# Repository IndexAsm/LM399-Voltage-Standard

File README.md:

# LM399 10V Voltage Standard

10V Voltage Standard used to calibrate equipment.

## Functions
  - Uptime tracking
  - Temperature tracking
  - Stores calibration data
  - USB connection
  - Status LED
  - Voltage & Current monitoring

## Specifications
  - Calibrated 10 V reference output with ppm-level stability target
  - Low tempco (I am aiming for < 5ppm but that requires testing)
  - Low long term drift ( Also requires testing, in order to determine the value)

## Calibration
  - Short pins on CAL_EN header.
  - Measure the output and adjust the binary trim network accordingly.
  - Connect it to a computer and write changes to eeprom (a special program will be created after constructing the first prototype).
  - Open CAL_EN header.
  - Done!

## Reference
LM399 is chosen as the main reference, which is later amplified to precise 10V with LT1001. It uses precise Z Foil resistors for gain.
It has an internal heater to keep it at stable temperature, in order to prevent output drift.

## PCB
I decided to go with a 4 layer board. This way I can make L2 a solid ground and L3 power. It not only simplifies routing but also improves performance
There is a little space left empty which also has a purpose. This way I can keep digital and power electronics away from sensitive reference part. Voltage regulator can heat up. If they were close to precision section, the trim network would heat up, which would result in output drift.

The reference section has an exposed copper area on the first layer to attach aluminum shielding.

Also there are a few text fields to input measurements, when the device is first calibrated.

## Gallery

## Software
I used Kicad to design this board.

## [BOM](LM399VoltageStandard.csv)
Total cost: 473,59zł + shipping
That is $127.10 USD
Some parts are left with no price or link. That means I already have them so I did not include them in price calculation.

## Credits
I relied on MarcoReps's videos to learn everything in order to make this project.

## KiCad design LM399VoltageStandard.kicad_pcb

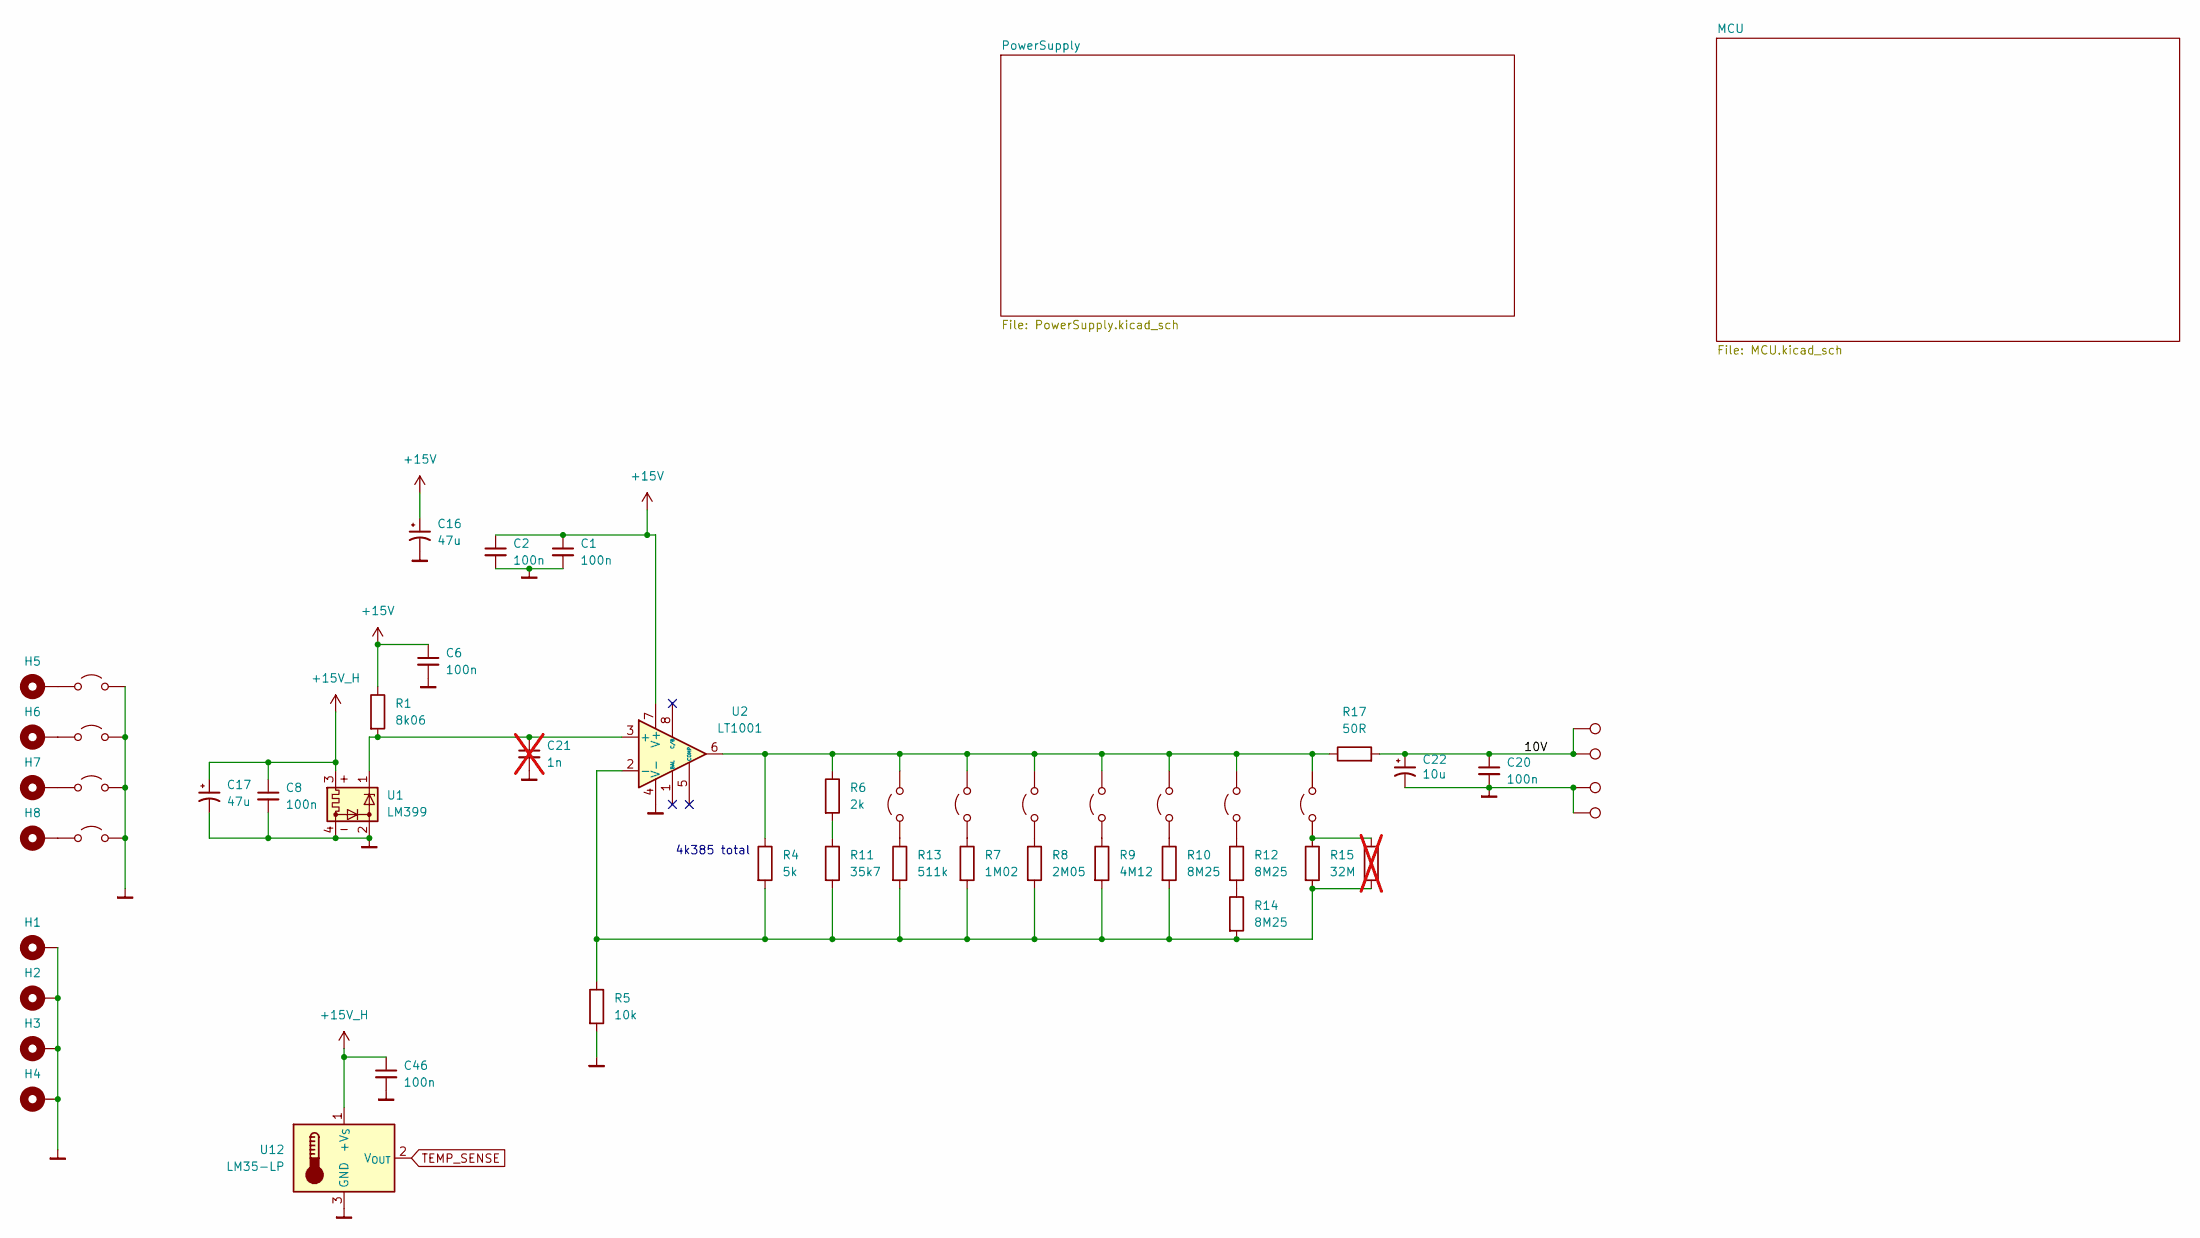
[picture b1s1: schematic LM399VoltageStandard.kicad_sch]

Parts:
C1, C2, C6, C8, C20, C46: 100n; C_0603_1608Metric
C16, C17: 47u; CP_Radial_D5.0mm_P2.00mm
C21: 1n; C_0603_1608Metric; not fitted
C22: 10u; CP_EIA-7132-20_AVX-U
H1, H2, H3, H4, H5, H6, H7, H8: MountingHole_Pad; MountingHole_3.2mm_M3_Pad_TopBottom
JP8, JP9, JP10, JP11, JP12, JP13, JP14, JP15, JP16, JP17, JP18: Jumper_2_Open; SolderJumper-2_P1.3mm_Open_RoundedPad1.0x1.5mm
R1: 8k06; R_0603_1608Metric
R4: 5k; ZFoilResistor
R5: 10k; R_Axial_DIN0207_L6.3mm_D2.5mm_P10.16mm_Horizontal
R6: 2k; R_1206_3216Metric
R7: 1M02; R_0805_2012Metric
R8: 2M05; R_0805_2012Metric
R9: 4M12; R_Axial_DIN0207_L6.3mm_D2.5mm_P10.16mm_Horizontal
R10, R12, R14: 8M25; R_Axial_DIN0204_L3.6mm_D1.6mm_P7.62mm_Horizontal
R11: 35k7; R_0603_1608Metric
R13: 511k; R_0603_1608Metric
R15: 32M; R_Axial_DIN0207_L6.3mm_D2.5mm_P10.16mm_Horizontal
R16: 32M; R_0805_2012Metric; not fitted
R17: 50R; R_0805_2012Metric
TP3, TP6, TP7, TP8: TestPoint; TestPoint_Pad_4.0x4.0mm
U1: LM399; Analog_TO-46-4_ThermalShield
U2: LT1001; SOIC-8_3.9x4.9mm_P1.27mm
U12: LM35-LP; TO-92_Inline

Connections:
+15V: C1.1, C2.1, C6.1, C16.1, R1.1, U2.7 (V+); also elsewhere on the board
+15V_H: C8.1, C17.1, C46.1, U1.3, U12.1 (+V_{S}); also elsewhere on the board
/10V: C20.1, C22.1, R17.2, TP3.1 (1_1), TP7.1 (1_1)
Masa: C1.2, C2.2, C6.2, C8.2, C16.2, C17.2, C20.2, C21.2, C22.2, C46.2, H1.1 (1_1), H2.1 (1_1), H3.1 (1_1), H4.1 (1_1), JP15.2 (B), JP16.2 (B), JP17.2 (B), JP18.2 (B), R5.2, TP6.1 (1_1), TP8.1 (1_1), U1.2, U1.4, U2.4 (V-), U12.3 (GND); also elsewhere on the board
unnamed: JP8.1 (A), R13.1
unnamed: JP9.1 (A), R7.1
unnamed: JP10.1 (A), R8.1
unnamed: JP8.2 (B), JP9.2 (B), JP10.2 (B), JP11.2 (B), JP12.2 (B), JP13.2 (B), JP14.2 (B), R4.1, R6.1, R17.1, U2.6
unnamed: JP11.1 (A), R9.1
unnamed: JP12.1 (A), R10.1
unnamed: JP13.1 (A), R12.1
unnamed: JP14.1 (A), R15.1, R16.1
unnamed: H5.1 (1_1), JP15.1 (A)
unnamed: H6.1 (1_1), JP16.1 (A)
unnamed: H7.1 (1_1), JP17.1 (A)
unnamed: H8.1 (1_1), JP18.1 (A)
unnamed: R6.2, R11.1
unnamed: R12.2, R14.1
unnamed: C21.1, R1.2, U1.1, U2.3 (+)
unnamed: R4.2, R5.1, R7.2, R8.2, R9.2, R10.2, R11.2, R13.2, R14.2, R15.2, R16.2, U2.2 (-)
TEMP_SENSE: U12.2 (V_{OUT}); also elsewhere on the board

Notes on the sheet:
4k385 total

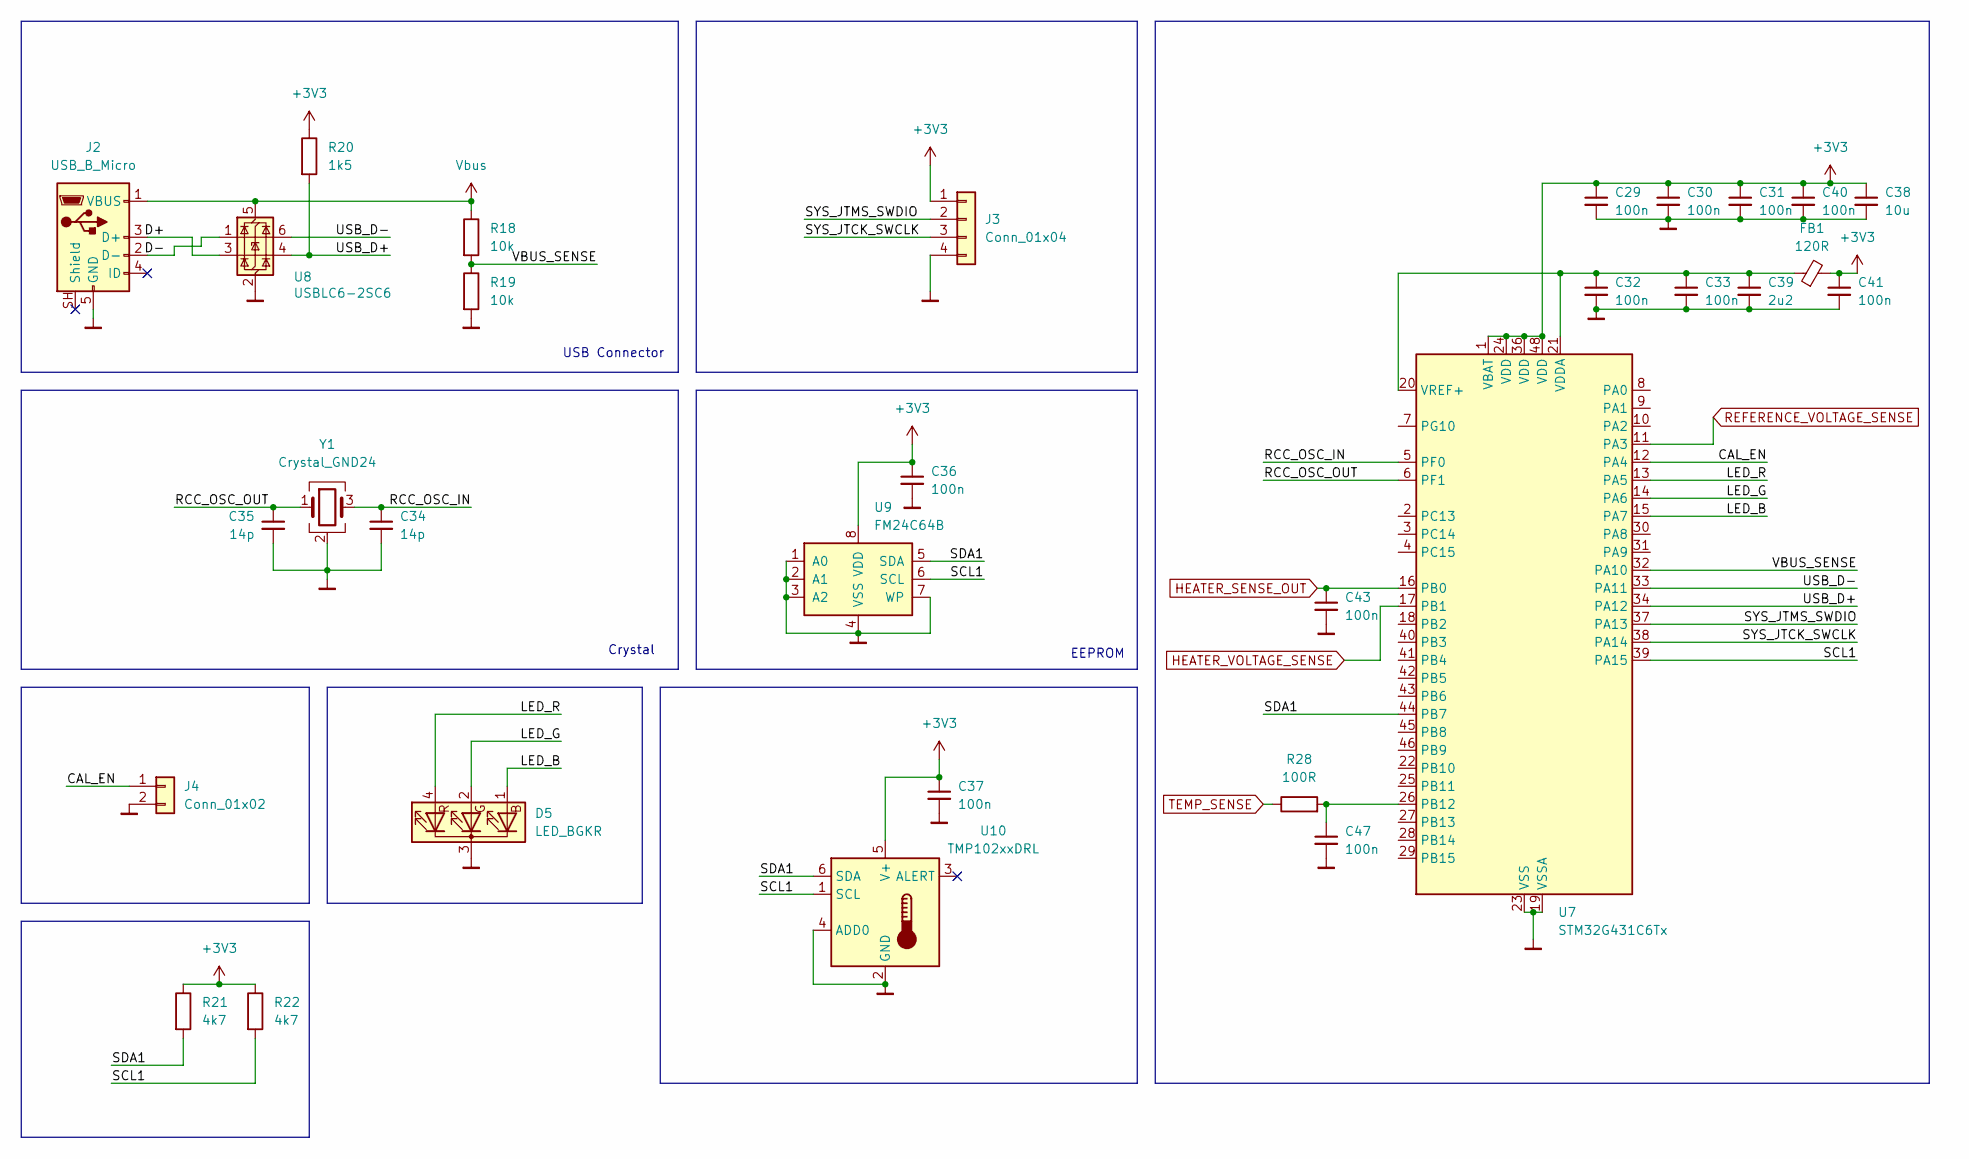
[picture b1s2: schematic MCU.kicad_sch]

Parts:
C29, C30, C31, C32, C33, C36, C37, C40, C41, C43, C47: 100n; C_0603_1608Metric
C34, C35: 14p; C_0603_1608Metric
C38: 10u; C_0805_2012Metric
C39: 2u2; C_0603_1608Metric
D5: LED_BGKR; LED_D5.0mm-4_RGB_Wide_Pins
FB1: 120R; L_0603_1608Metric
J2: USB_B_Micro; USB_Micro-B_Technik_TWP-4002D-H3
J3: Conn_01x04; PinHeader_1x04_P2.54mm_Vertical
J4: Conn_01x02; PinHeader_1x02_P2.54mm_Vertical
R18, R19: 10k; R_0603_1608Metric
R20: 1k5; R_0603_1608Metric
R21, R22: 4k7; R_0603_1608Metric
R28: 100R; R_0603_1608Metric
U7: STM32G431C6Tx; LQFP-48_7x7mm_P0.5mm
U8: USBLC6-2SC6; SOT-23-6
U9: FM24C64B; SOIC-8_3.9x4.9mm_P1.27mm
U10: TMP102xxDRL; SOT-563
Y1: Crystal_GND24; Crystal_SMD_EuroQuartz_X22-4Pin_2.5x2.0mm_HandSoldering

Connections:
+3V3: C29.1, C30.1, C31.1, C36.1, C37.1, C38.1, C40.1, C41.1, FB1.2, J3.1, R20.1, R21.1, R22.1, U7.1 (VBAT), U7.24 (VDD), U7.36 (VDD), U7.48 (VDD), U9.8 (VDD), U10.5 (V+); also elsewhere on the board
/MCU/CAL_EN: J4.1, U7.12 (PA4)
/MCU/D+: J2.3 (D+), U8.3 (I/O2)
/MCU/D-: J2.2 (D-), U8.1 (I/O1)
/MCU/LED_B: D5.1 (BA), U7.15 (PA7)
/MCU/LED_G: D5.2 (GA), U7.14 (PA6)
/MCU/LED_R: D5.4 (RA), U7.13 (PA5)
/MCU/RCC_OSC_IN: C34.1, U7.5 (PF0), Y1.3
/MCU/RCC_OSC_OUT: C35.1, U7.6 (PF1), Y1.1
/MCU/SCL1: R22.2, U7.39 (PA15), U9.6 (SCL), U10.1 (SCL)
/MCU/SDA1: R21.2, U7.44 (PB7), U9.5 (SDA), U10.6 (SDA)
/MCU/SYS_JTCK_SWCLK: J3.3, U7.38 (PA14)
/MCU/SYS_JTMS_SWDIO: J3.2, U7.37 (PA13)
/MCU/USB_D+: R20.2, U7.34 (PA12), U8.4 (I/O2)
/MCU/USB_D-: U7.33 (PA11), U8.6 (I/O1)
/MCU/VBUS_SENSE: R18.2, R19.1, U7.32 (PA10)
HEATER_SENSE_OUT: C43.1, U7.16 (PB0); also elsewhere on the board
HEATER_VOLTAGE_SENSE: U7.17 (PB1); also elsewhere on the board
Masa: C29.2, C30.2, C31.2, C32.2, C33.2, C34.2, C35.2, C36.2, C37.2, C38.2, C39.2, C40.2, C41.2, C43.2, C47.2, D5.3 (K), J2.5 (GND), J3.4, J4.2, R19.2, U7.19 (VSSA), U7.23 (VSS), U7.35 (VSS), U7.47 (VSS), U8.2 (GND), U9.1 (A0), U9.2 (A1), U9.3 (A2), U9.4 (VSS), U9.7 (WP), U10.2 (GND), U10.4 (ADD0), Y1.2 (G), Y1.4 (G); also elsewhere on the board
unnamed: C47.1, R28.2, U7.26 (PB12)
unnamed: C32.1, C33.1, C39.1, FB1.1, U7.20 (VREF+), U7.21 (VDDA)
REFERENCE_VOLTAGE_SENSE: U7.11 (PA3); also elsewhere on the board
TEMP_SENSE: R28.1; also elsewhere on the board
Vbus: J2.1 (VBUS), R18.1, U8.5 (VBUS)

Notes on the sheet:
Crystal
EEPROM
USB Connector

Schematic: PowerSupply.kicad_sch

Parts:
C4, C5, C48: 1000u; CP_Radial_D10.0mm_P3.80mm
C7, C10, C18, C19, C24, C25, C26, C42, C44, C45: 100n; C_0603_1608Metric
C9, C14, C23: 47u; CP_Radial_D5.0mm_P2.00mm
C12, C13: 100n; C_0805_2012Metric
C15: PUUP3JH; CP_Radial_D10.0mm_P3.80mm
C27, C28: 10u; C_0805_2012Metric
D2, D3, D4: PUUP3JH; TO-277A
D6: B40C2300-1500A; Diode_Bridge_19.0x3.5x10.0mm_P5.0mm
J1: Screw_Terminal_01x02; TerminalBlock_MaiXu_MX126-5.0-02P_1x02_P5.00mm
R23: 0R1; R_0805_2012Metric
R24, R27: 4k; R_0603_1608Metric
R25, R26: 20k; R_0603_1608Metric
TP2, TP4, TP5: TestPoint; TestPoint_Pad_D1.5mm
U4: TLV75533PDRV; WSON-6-1EP_2x2mm_P0.65mm_EP1x1.6mm
U5, U13: LM7815; TO-220-3_Vertical
U6: LM7805_TO220; TO-220-3_Vertical
U11: INA180B3; SOT-23-5

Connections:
+3V3: C26.1, C27.1, C42.1, U4.1 (OUT), U11.5 (V+); also elsewhere on the board
+5V: C18.1, C24.1, C28.1, U4.4 (EN), U4.6 (IN), U6.3 (VO)
+15V: C9.1, C10.1, R25.1, TP4.1 (1_1), U13.3 (VO); also elsewhere on the board
+15V_H: C13.1, C14.1, R26.1, TP2.1 (1_1), U5.3 (VO); also elsewhere on the board
/PowerSupply/HEATER_SENSE_L: C12.1, C15.1, R23.2, U5.1 (VI), U11.3 (-)
HEATER_SENSE_OUT: U11.4; also elsewhere on the board
HEATER_VOLTAGE_SENSE: C45.1, R26.2, R27.1; also elsewhere on the board
Masa: C4.2, C5.2, C7.2, C9.2, C10.2, C12.2, C13.2, C14.2, C15.2, C18.2, C19.2, C23.2, C24.2, C25.2, C26.2, C27.2, C28.2, C42.2, C44.2, C45.2, C48.2, D6.1 (-), R24.2, R27.2, TP5.1 (1_1), U4.3 (GND), U4.7 (GND), U5.2 (GND), U6.2 (GND), U11.2 (GND), U13.2 (GND); also elsewhere on the board
unnamed: D6.3, J1.1
unnamed: D6.2, J1.2
REFERENCE_VOLTAGE_SENSE: C44.1, R24.1, R25.2; also elsewhere on the board
VIN: C4.1, C5.1, C7.1, C19.1, C23.1, C25.1, C48.1, D6.4 (+), R23.1, U6.1 (VI), U11.1 (+), U13.1 (VI)

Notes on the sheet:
DP-241-4-16
Voltage Monitoring
Rectifier and filtering
Current Monitoring
Digital supply
Reference 15V
Heater 15V

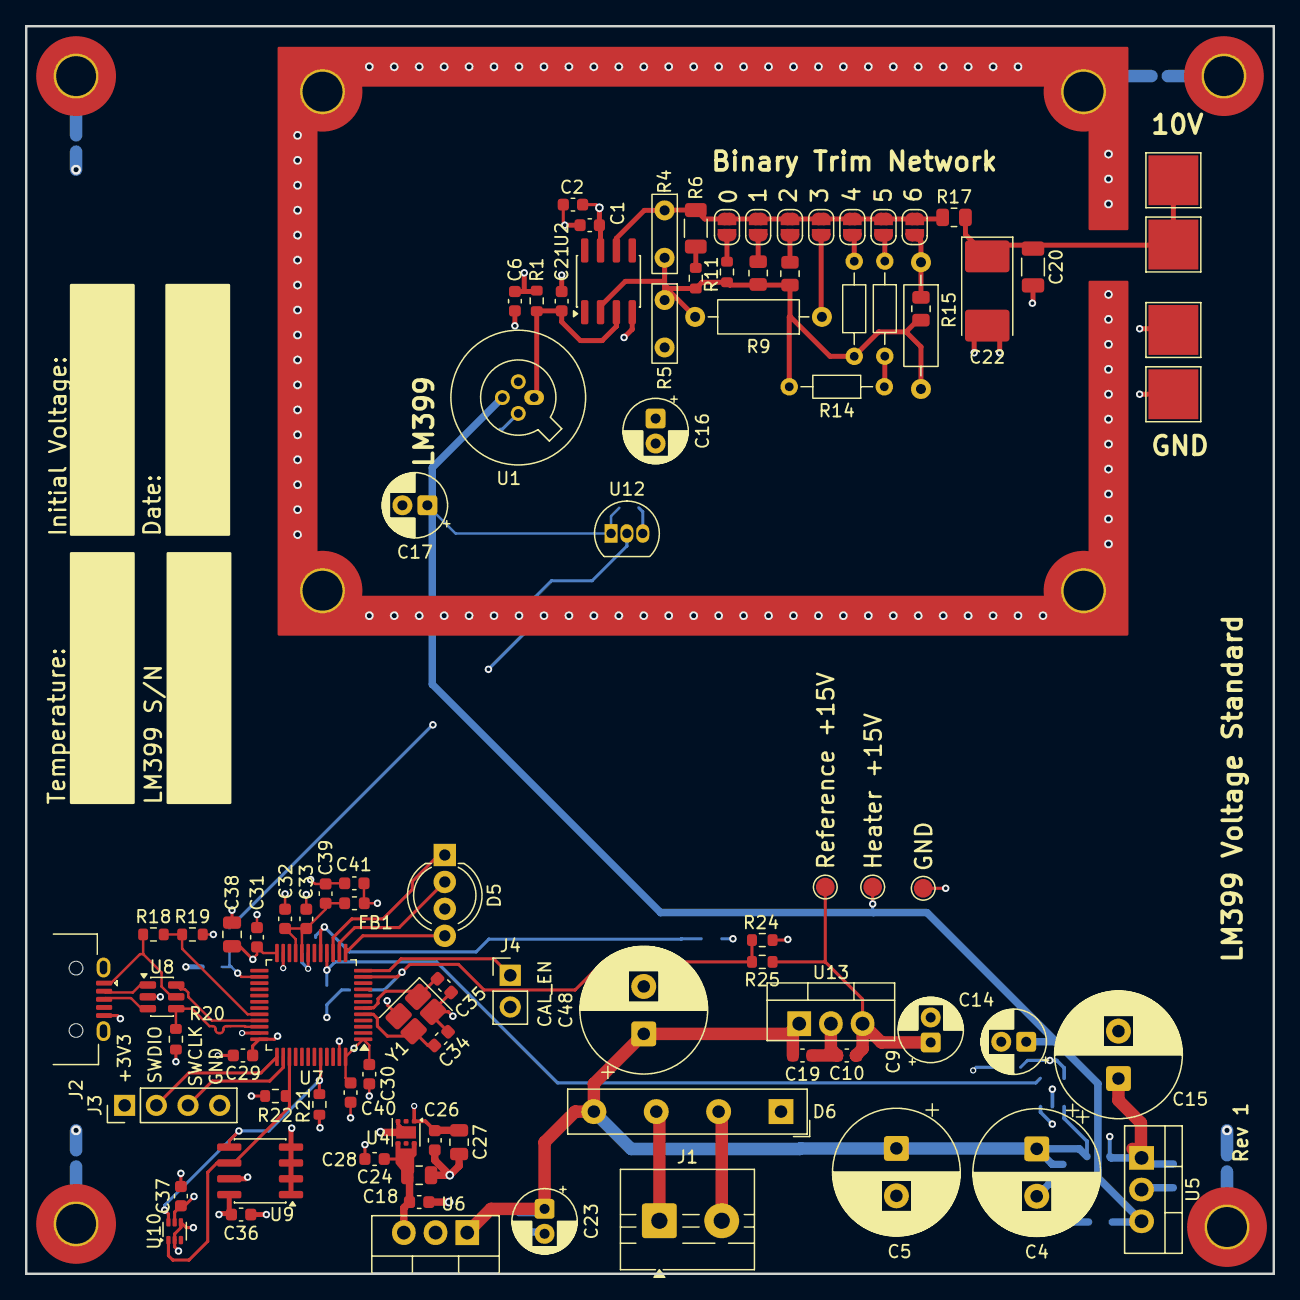
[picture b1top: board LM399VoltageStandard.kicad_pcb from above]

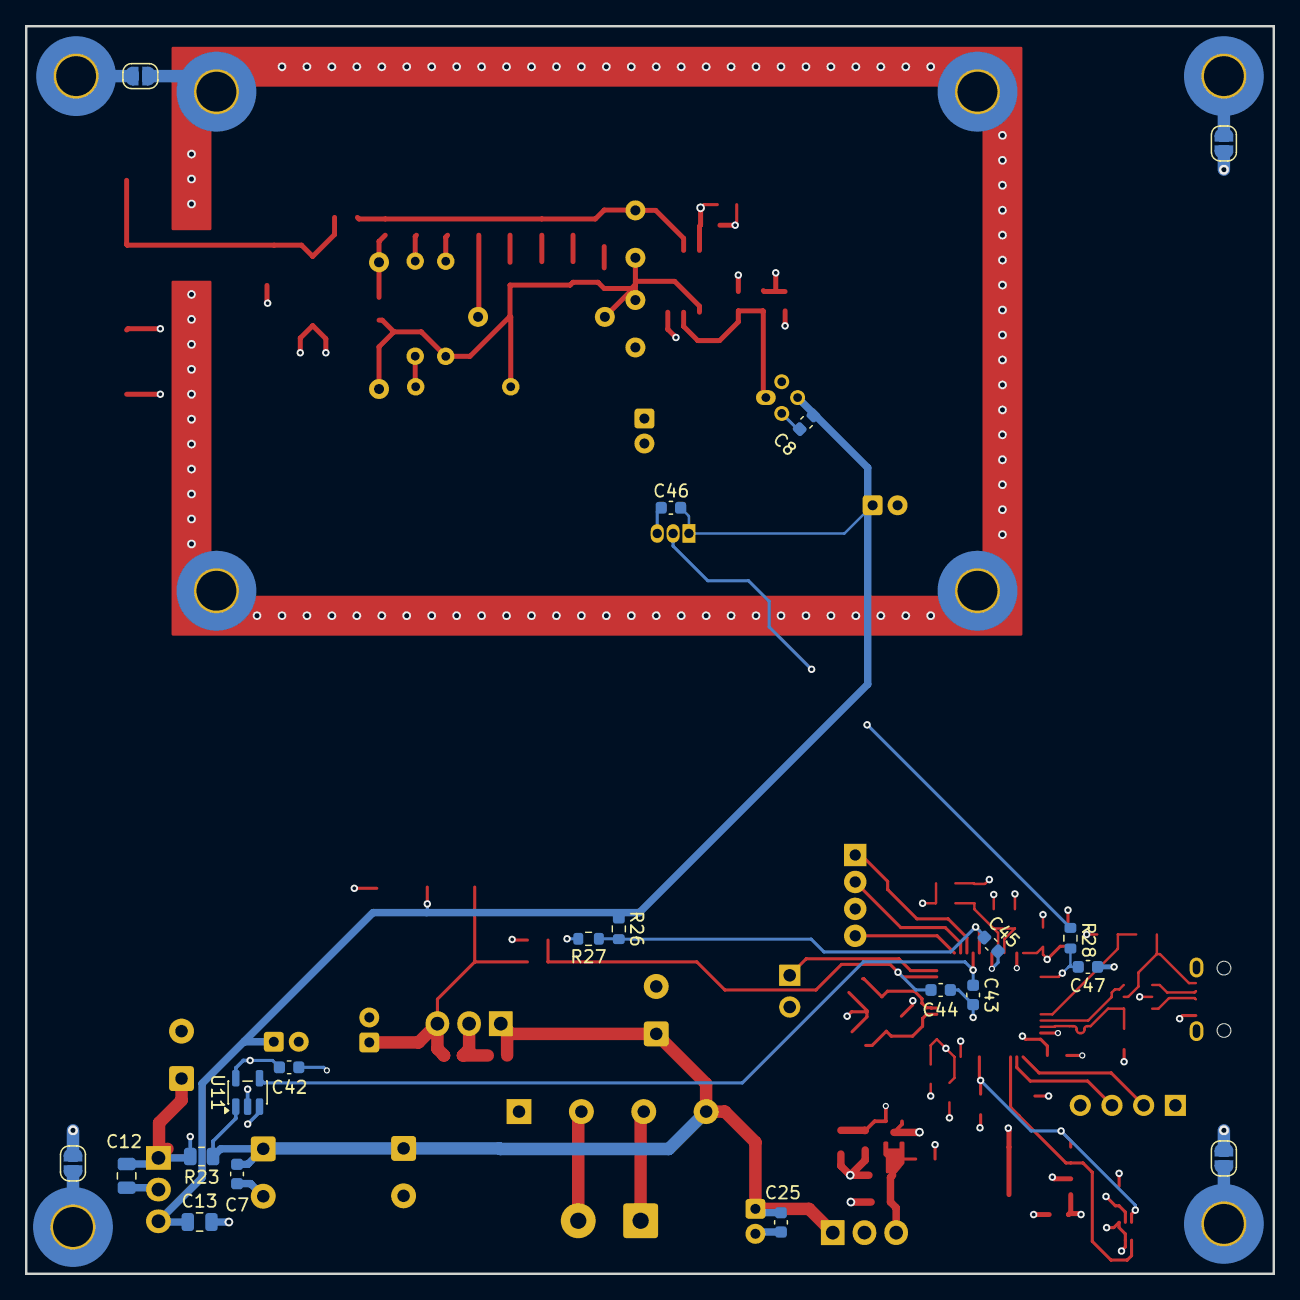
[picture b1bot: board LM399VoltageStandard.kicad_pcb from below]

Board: 4 copper layers, 100.0 x 100.0 mm, 118 parts (20 on the bottom side), 48 nets.

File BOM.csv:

"Reference","Qty","Value","DNP","Price","Link","Footprint"
"C1,C2,C6,C7,C8,C10,C11,C18,C19,C24,C25,C26,C29,C30,C31,C32,C33,C36,C37,C40,C41,C42,C43,C44,C45,C46,C47","27","100n","","","","Capacitor_SMD:C_0603_1608Metric"
"C4,C5,C15","3","1000u","","","","Capacitor_THT:CP_Radial_D10.0mm_P3.80mm"
"C9,C14,C16,C17,C23","5","47u","","","","Capacitor_THT:CP_Radial_D5.0mm_P2.00mm"
"C12,C13","2","100n","","","","Capacitor_SMD:C_0805_2012Metric"
"C20","1","100n","","1,26zł","https://www.mouser.pl/en/ProductDetail/Murata-Electronics/GR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","Capacitor_SMD:C_1206_3216Metric"
"C21","1","1n","DNP","","","Capacitor_SMD:C_0603_1608Metric"
"C22","1","10u","","","https://www.mouser.pl/ProductDetail/KEMET/A700V106M016ATE045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","Capacitor_Tantalum_SMD:CP_EIA-7132-20_AVX-U"
"C27,C28,C38","3","10u","","1,51zł","https://www.mouser.pl/en/ProductDetail/Samsung-Electro-Mecha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","Capacitor_SMD:C_0805_2012Metric"
"C34,C35","2","14p","","","","Capacitor_SMD:C_0603_1608Metric"
"C39","1","2u2","","0,36zł ","https://www.mouser.pl/en/ProductDetail/Samsung-Electro-Mecha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","Capacitor_SMD:C_0603_1608Metric"
"D6","1","KBP206G","","15.32zł","https://www.mouser.pl/en/ProductDetail/Taiwan-Semiconductor/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", ""
"D5","1","LED_BGKR","","0,97zł","https://www.mouser.pl/en/ProductDetail/Soldered/100105?qs=%2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","LED_THT:LED_D5.0mm-4_RGB_Wide_Pins"
"FB1","1","120R","","0,36zł ","https://www.mouser.pl/en/ProductDetail/TDK/MMZ1608S121ATA00?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","Inductor_SMD:L_0603_1608Metric"
"J1","1","Screw_Terminal_01x02","","","","TerminalBlock:TerminalBlock_MaiXu_MX126-5.0-02P_1x02_P5.00mm"
"J2","1","USB_B_Micro","","","","Connector_USB:USB_Micro-B_Technik_TWP-4002D-H3"
"J3","1","Conn_01x04","","","","Connector_PinHeader_2.54mm:PinHeader_1x04_P2.54mm_Vertical"
"J4","1","Conn_01x02","","","","Connector_PinHeader_2.54mm:PinHeader_1x02_P2.54mm_Vertical"
"JP8,JP9,JP10,JP11,JP12,JP13,JP14,JP15,JP16,JP17,JP18","11","Jumper_2_Open","","","","Jumper:SolderJumper-2_P1.3mm_Open_RoundedPad1.0x1.5mm"
"R1","1","8k06","","2,71zł","https://www.mouser.pl/ProductDetail/TE-Connectivity-Holswort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","Resistor_SMD:R_0603_1608Metric"
"R2","1","250","","","","Resistor_SMD:R_0603_1608Metric"
"R3","1","150k","","","","Resistor_SMD:R_0603_1608Metric"
"R4","1","5k","","141,58zł","https://www.mouser.pl/ProductDetail/Vishay-Precision-Group-F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","LM399VoltageStandard:ZFoilResistor"
"R5","1","10k","","104,75zł","https://www.mouser.pl/ProductDetail/Vishay-Precision-Group-F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","Resistor_THT:R_Axial_DIN0207_L6.3mm_D2.5mm_P10.16mm_Horizontal"
"R6","1","2k","","9,41zł","https://www.mouser.pl/ProductDetail/SEI-Stackpole/RNCF1206TK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","Resistor_SMD:R_1206_3216Metric"
"R7","1","1M02","","1,37zł","https://www.mouser.pl/ProductDetail/YAGEO/RT0805BRD071M02L?q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","Resistor_SMD:R_0805_2012Metric"
"R8","1","2M05","","1,37zł","https://www.mouser.pl/ProductDetail/Kamaya/RGC1-10C2054FTP?q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","Resistor_SMD:R_0805_2012Metric"
"R9","1","4M12","","10,67zł","https://www.mouser.pl/ProductDetail/Vishay-Dale/CMF554M1200F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","Resistor_THT:R_Axial_DIN0207_L6.3mm_D2.5mm_P10.16mm_Horizontal"
"R10,R12,R14","3","8M25","","13,70zł","https://www.mouser.pl/ProductDetail/Xicon/270-8.25M-RC?qs=sG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","Resistor_THT:R_Axial_DIN0204_L3.6mm_D1.6mm_P7.62mm_Horizontal"
"R11","1","35k7","","3,72zł","https://www.mouser.pl/ProductDetail/TE-Connectivity-Holswort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","Resistor_SMD:R_0603_1608Metric"
"R13","1","511k","","2,13zł","https://www.mouser.pl/ProductDetail/TE-Connectivity-Holswort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","Resistor_SMD:R_0603_1608Metric"
"R15","1","32M","","10,67zł","https://www.mouser.pl/ProductDetail/Vishay-Dale/CMF554M1200F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","Resistor_THT:R_Axial_DIN0207_L6.3mm_D2.5mm_P10.16mm_Horizontal"
"R16","1","32M","DNP","","https://www.mouser.pl/ProductDetail/Kamaya/RGC1-10C2054FTP?q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","Resistor_SMD:R_0805_2012Metric"
"R17","1","50R","","1,37","https://www.mouser.pl/ProductDetail/YAGEO/RT0805BRD071M02L?q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","Resistor_SMD:R_0805_2012Metric"
"R18,R19","2","10k","","","","Resistor_SMD:R_0603_1608Metric"
"R20","1","1k5","","","","Resistor_SMD:R_0603_1608Metric"
"R21,R22","2","4k7","","","","Resistor_SMD:R_0603_1608Metric"
"R23","1","0R1","","0,76zł","https://www.mouser.pl/en/ProductDetail/Panasonic/ERJ-6DSJR10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","Resistor_SMD:R_0805_2012Metric"
"R24,R27","2","4k","","","","Resistor_SMD:R_0603_1608Metric"
"R25,R26","2","20k","","","","Resistor_SMD:R_0603_1608Metric"
"R28","1","100R","","","","Resistor_SMD:R_0603_1608Metric"
"TP2,TP4,TP5","3","TestPoint","","","","TestPoint:TestPoint_Pad_D1.5mm"
"TP3,TP6,TP7,TP8","4","TestPoint","","","","TestPoint:TestPoint_Pad_4.0x4.0mm"
"U1","1","LM399","","","https://www.mouser.pl/en/ProductDetail/Analog-Devices/LM399A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","Package_TO_SOT_THT:Analog_TO-46-4_ThermalShield"
"U2","1","LT1001","","22,51zł","https://www.mouser.pl/ProductDetail/Analog-Devices/LT1001CS8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","Package_SO:SOIC-8_3.9x4.9mm_P1.27mm"
"U4","1","TLV75533PDRV","","1,63zł","https://www.mouser.pl/en/ProductDetail/Texas-Instruments/TLV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","Package_SON:WSON-6-1EP_2x2mm_P0.65mm_EP1x1.6mm"
"U5, U13","1","LM7815","","","","Package_TO_SOT_THT:TO-220-3_Vertical"
"U6","1","LM7805_TO220","","","","Package_TO_SOT_THT:TO-220-3_Vertical"
"U7","1","STM32G431C6Tx","","16,72zł","https://www.mouser.pl/en/ProductDetail/STMicroelectronics/ST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","Package_QFP:LQFP-48_7x7mm_P0.5mm"
"U8","1","USBLC6-2SC6","","1,59zł","https://www.mouser.pl/en/ProductDetail/STMicroelectronics/US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","Package_TO_SOT_SMD:SOT-23-6"
"U9","1","FM24C64B","","1,12zł","https://www.mouser.pl/en/ProductDetail/STMicroelectronics/M2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","Package_SO:SOIC-8_3.9x4.9mm_P1.27mm"
"U10","1","TMP102xxDRL","","4,15zł","https://www.mouser.pl/en/ProductDetail/Texas-Instruments/TMP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","Package_TO_SOT_SMD:SOT-563"
"U11","1","INA180B3","","2,28zł","https://www.mouser.pl/en/ProductDetail/Texas-Instruments/INA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","Package_TO_SOT_SMD:SOT-23-5"
"U12","1","LM35-LP","","","","Package_TO_SOT_THT:TO-92_Inline"
"Y1","1","Crystal_GND24","","0,87zł","https://www.mouser.pl/en/ProductDetail/Eaton-Electronics/E2X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","Crystal:Crystal_SMD_EuroQuartz_X22-4Pin_2.5x2.0mm_HandSoldering"
"","1","PCB & shipping","","","",""
"","1"," DP-241-4-16 ","","65,65zł","",""

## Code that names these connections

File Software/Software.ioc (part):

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Mcu.Name=STM32G431C(6-8-B)Tx
Mcu.Package=LQFP48
Mcu.UserName=STM32G431C6Tx
PA10.Signal=GPIO_Input
PA11.Mode=Device
PA11.Signal=USB_DM
PA12.Mode=Device
PA12.Signal=USB_DP
PA13.Mode=Serial_Wire
PA13.Signal=SYS_JTMS-SWDIO
PA14.Mode=Serial_Wire
PA14.Signal=SYS_JTCK-SWCLK
PA15.Mode=I2C
PA15.Signal=I2C1_SCL
PA3.GPIOParameters=GPIO_Label
PA3.GPIO_Label=REFERENCE_VOLTAGE_SENSE
PA3.Mode=IN4-Single-Ended
PA3.Signal=ADC1_IN4
PA4.GPIOParameters=GPIO_Label
PA4.GPIO_Label=CAL_EN
PA4.Signal=GPIO_Output
PA5.GPIOParameters=GPIO_Label
PA5.GPIO_Label=LED_R
PA5.Signal=GPIO_Output
PA6.GPIOParameters=GPIO_Label
PA6.GPIO_Label=LED_G
PA6.Signal=GPIO_Output
PA7.GPIOParameters=GPIO_Label
PA7.GPIO_Label=LED_B
PA7.Signal=GPIO_Output
PB0.GPIOParameters=GPIO_Label
PB0.GPIO_Label=HEATER_CURRENT_SENSE
PB0.Mode=IN15-Single-Ended
PB0.Signal=ADC1_IN15
PB1.GPIOParameters=GPIO_Label
PB1.GPIO_Label=HEATER_VOLTAGE_SENSE
PB1.Mode=IN12-Single-Ended
PB1.Signal=ADC1_IN12
PB12.GPIOParameters=GPIO_Label
PB12.GPIO_Label=TEMP_SENSE
PB12.Mode=IN11-Single-Ended
PB12.Signal=ADC1_IN11
PB7.Mode=I2C
PB7.Signal=I2C1_SDA
PF0-OSC_IN.Mode=HSE-External-Oscillator
PF0-OSC_IN.Signal=RCC_OSC_IN
PF1-OSC_OUT.Mode=HSE-External-Oscillator
PF1-OSC_OUT.Signal=RCC_OSC_OUT
RCC.HSE_VALUE=16000000
RCC.SYSCLKFreq_VALUE=160000000
RCC.SYSCLKSource=RCC_SYSCLKSOURCE_PLLCLK
board=custom
